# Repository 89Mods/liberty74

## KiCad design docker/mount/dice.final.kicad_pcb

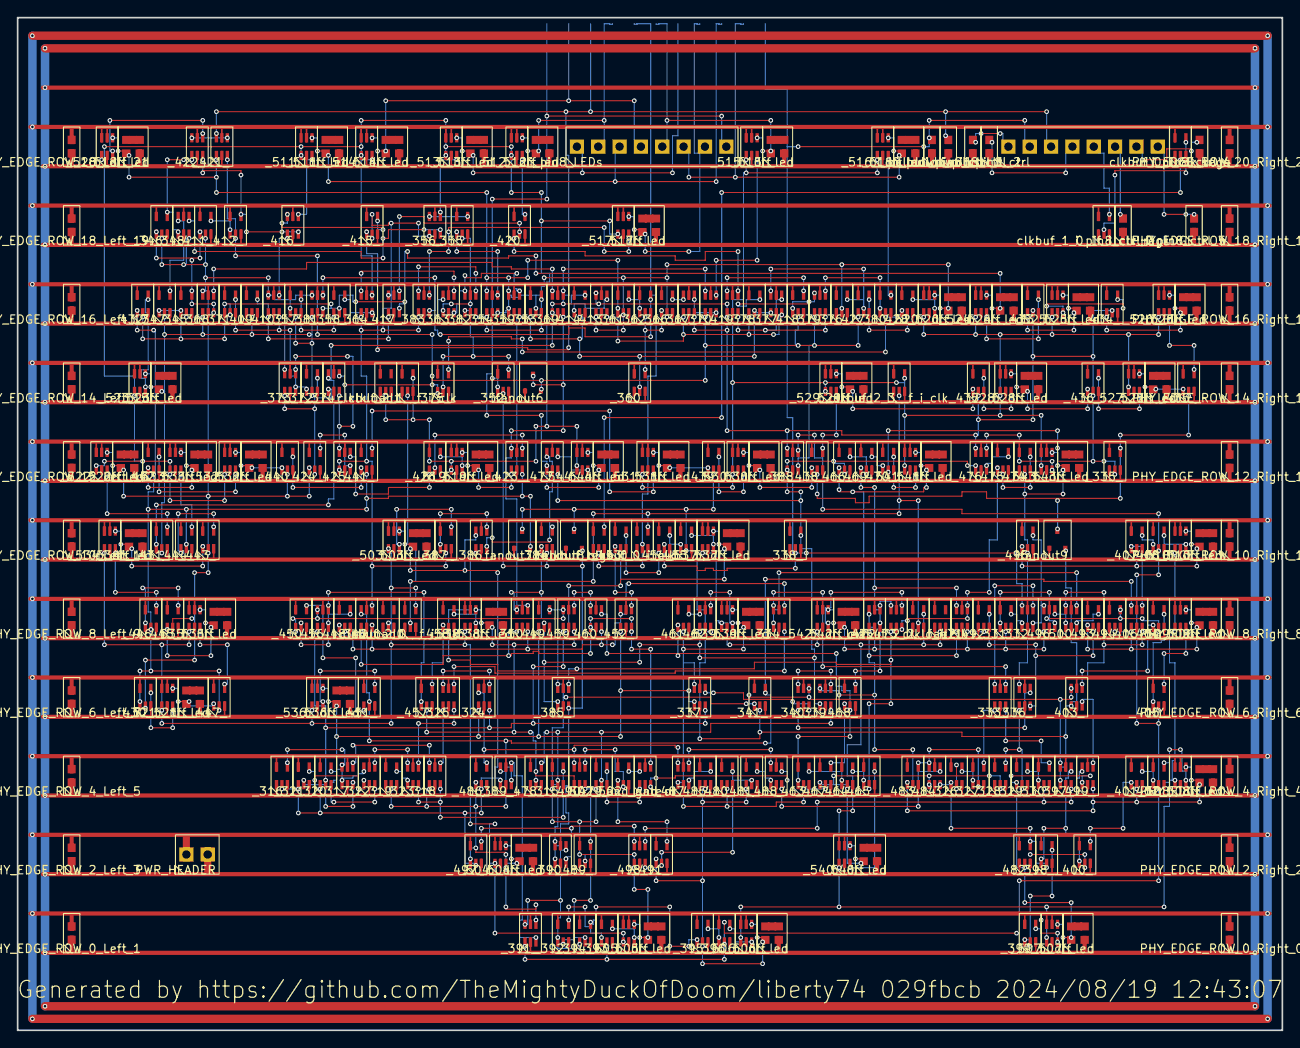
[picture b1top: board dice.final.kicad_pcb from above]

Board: 2 copper layers, 150.5 x 120.5 mm, 313 parts (0 on the bottom side), 246 nets.

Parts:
PHY_EDGE_ROW_0_Left_1, PHY_EDGE_ROW_0_Right_0, PHY_EDGE_ROW_2_Left_3, PHY_EDGE_ROW_2_Right_2, PHY_EDGE_ROW_4_Left_5, PHY_EDGE_ROW_4_Right_4, PHY_EDGE_ROW_6_Left_7, PHY_EDGE_ROW_6_Right_6, PHY_EDGE_ROW_8_Left_9, PHY_EDGE_ROW_8_Right_8, PHY_EDGE_ROW_10_Left_11, PHY_EDGE_ROW_10_Right_10, PHY_EDGE_ROW_12_Left_13, PHY_EDGE_ROW_12_Right_12, PHY_EDGE_ROW_14_Left_15, PHY_EDGE_ROW_14_Right_14, PHY_EDGE_ROW_16_Left_17, PHY_EDGE_ROW_16_Right_16, PHY_EDGE_ROW_18_Left_19, PHY_EDGE_ROW_18_Right_18, PHY_EDGE_ROW_20_Left_21, PHY_EDGE_ROW_20_Right_20: PWR_CAP; PWR_CAP_N
PWR_HEADER: PWR_HEADER; PWR_HEADER_N
_315_, _329_, _357_, _361_, _392_, _395_, _398_, _401_, _404_, _407_, _440_, _443_, _445_, _450_, _453_, _457_, _461_, _464_, _469_, _475_, _483_, _491_, _493_, _495_: XOR2_74LVC1G86; XOR2_74LVC1G86_N
_316_, _319_, _328_, _335_, _338_, _360_, _371_, _376_, _409_, _474_, _478_, _480_, _482_, _485_, _489_, _492_, _494_: INV_74LVC1G04; INV_74LVC1G04_N
_317_, _334_, _336_, _339_, _342_, _359_, _379_, _385_, _391_, _406_, _423_, _425_, _452_, _456_, _459_, _460_, _462_, _473_, _498_, _499_: AND3_74LVC1G11; AND3_74LVC1G11_N
_318_, _323_, _325_, _340_, _350_, _373_, _390_, _397_, _403_, _410_, _417_, _471_: NAND3_74LVC1G10; NAND3_74LVC1G10_N
_320_, _327_, _341_, _362_, _366_, _375_, _393_, _396_, _399_, _402_, _405_, _408_, _414_, _420_, _427_, _430_, _432_, _435_, _438_, _439_, _441_, _442_, _444_, _446_, _447_, _448_, _449_, _451_, _455_, _458_, _463_, _465_, _466_, _467_, _468_, _479_, _481_, _497_, _502__and_gate: AND2_74LVC1G08; AND2_74LVC1G08_N
_321_, _330_, _353_, _355_, _380_, _387_, _394_, _400_, _411_, _412_, _415_, _428_: NOR2_74LVC1G02; NOR2_74LVC1G02_N
_322_, _348_, _354_, _368_, _386_, _500_: MUX2_74LVC1G157; MUX2_74LVC1G157_N
_324_, _381_, _419_: OR3_74LVC1G332; OR3_74LVC1G332_N
_326_, _331_, _347_, _358_, _372_, _378_, _424_, _426_, _431_, _433_, _434_, _436_, _437_, _454_, _470_: OR2_74LVC1G32; OR2_74LVC1G32_N
_332_, _356_, _364_, _370_, _374_, _377_, _383_, _388_, _389_, _416_, _421_, _422_, _472_, _476_, _477_, _484_, _487_, _488_, _490_, _496_, _502__and_or: AO21_74LVC1G0832; AO21_74LVC1G0832_N
_333_, _337_, _363_, _367_, _369_, _382_, _413_: NOR3_74LVC1G27; NOR3_74LVC1G27_N
_345_, _346_, _352_, _384_, _418_, _486_: NAND2_74LVC1G00; NAND2_74LVC1G00_N
_503__dff, _504__dff, _505__dff, _506__dff, _507__dff, _508__dff, _509__dff, _510__dff, _511__dff, _512__dff, _513__dff, _514__dff, _515__dff, _516__dff, _517__dff, _518__dff, _519__dff, _520__dff, _521__dff, _522__dff, _523__dff, _524__dff, _525__dff, _526__dff, _527__dff, _528__dff, _529__dff, _530__dff, _531__dff, _532__dff, _533__dff, _534__dff, _535__dff, _536__dff, _537__dff, _538__dff, _539__dff, _540__dff, _541__dff, _542__dff, _543__dff, _544__dff: DFF_74LVC1G175; DFF_74LVC1G175_N
_503__led, _504__led, _505__led, _506__led, _507__led, _508__led, _509__led, _510__led, _511__led, _512__led, _513__led, _514__led, _515__led, _516__led, _517__led, _518__led, _519__led, _520__led, _521__led, _522__led, _523__led, _524__led, _525__led, _526__led, _527__led, _528__led, _529__led, _530__led, _531__led, _532__led, _533__led, _534__led, _535__led, _536__led, _537__led, _538__led, _539__led, _540__led, _541__led, _542__led, _543__led, _544__led: Led_Res_0603; Led_Res_0603_N
clkbuf_0_i_clk, clkbuf_0_i_clk_regs, clkbuf_1_0__f_i_clk_regs, clkbuf_2_0__f_i_clk, clkbuf_2_1__f_i_clk, clkbuf_2_2__f_i_clk, clkbuf_2_3__f_i_clk: BUF_74LVC1G125; BUF_74LVC1G125_N
clkbuf_regs_0_: BUF_74LVC1G125; BUF_74LVC1G125_N
clkload0, clkload1, clkload2: BUF_74LVC1G125; BUF_74LVC1G125_N
fanout6, fanout7, fanout8, fanout9: DS9809PRSS3; DS9809PRSS3_N
i_pin8_LEDs, i_pin8_ctrl: PINOUT_8; PINOUT_8_N
i_pin8_ctrl_1, i_pin8_ctrl_2, i_pin8_ctrl_3, i_pin8_ctrl_4, i_pin8_ctrl_5: TIE_LO; TIE_LO_N
i_pulldown_roll: PULLDOWN_R0603; PULLDOWN_R0603_N
i_pulldown_rst: PULLDOWN_R0603; PULLDOWN_R0603_N

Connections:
GND: PHY_EDGE_ROW_0_Left_1.1 (GND), PHY_EDGE_ROW_0_Right_0.1 (GND), PHY_EDGE_ROW_2_Left_3.1 (GND), PHY_EDGE_ROW_2_Right_2.1 (GND), PHY_EDGE_ROW_4_Left_5.1 (GND), PHY_EDGE_ROW_4_Right_4.1 (GND), PHY_EDGE_ROW_6_Left_7.1 (GND), PHY_EDGE_ROW_6_Right_6.1 (GND), PHY_EDGE_ROW_8_Left_9.1 (GND), PHY_EDGE_ROW_8_Right_8.1 (GND), PHY_EDGE_ROW_10_Left_11.1 (GND), PHY_EDGE_ROW_10_Right_10.1 (GND), PHY_EDGE_ROW_12_Left_13.1 (GND), PHY_EDGE_ROW_12_Right_12.1 (GND), PHY_EDGE_ROW_14_Left_15.1 (GND), PHY_EDGE_ROW_14_Right_14.1 (GND), PHY_EDGE_ROW_16_Left_17.1 (GND), PHY_EDGE_ROW_16_Right_16.1 (GND), PHY_EDGE_ROW_18_Left_19.1 (GND), PHY_EDGE_ROW_18_Right_18.1 (GND), PHY_EDGE_ROW_20_Left_21.1 (GND), PHY_EDGE_ROW_20_Right_20.1 (GND), PWR_HEADER.2 (GND), _315_.3 (GND), _316_.1 (GND), _316_.3 (GND), _317_.2 (GND), _318_.2 (GND), _319_.1 (GND), _319_.3 (GND), _320_.3 (GND), _321_.3 (GND), _322_.2 (GND), _323_.2 (GND), _324_.2 (GND), _325_.2 (GND), _326_.3 (GND), _327_.3 (GND), _328_.1 (GND), _328_.3 (GND), _329_.3 (GND), _330_.3 (GND), _331_.3 (GND), _332_.2 (GND), _333_.2 (GND), _334_.2 (GND), _335_.1 (GND), _335_.3 (GND), _336_.2 (GND), _337_.2 (GND), _338_.1 (GND), _338_.3 (GND), _339_.2 (GND), _340_.2 (GND), _341_.3 (GND), _342_.2 (GND), _345_.3 (GND), _346_.3 (GND), _347_.3 (GND), _348_.2 (GND), _350_.2 (GND), _352_.3 (GND), _353_.3 (GND), _354_.2 (GND), _355_.3 (GND), _356_.2 (GND), _357_.3 (GND), _358_.3 (GND), _359_.2 (GND), _360_.1 (GND), _360_.3 (GND), _361_.3 (GND), _362_.3 (GND), _363_.2 (GND), _364_.2 (GND), _366_.3 (GND), _367_.2 (GND), _368_.2 (GND), _369_.2 (GND), _370_.2 (GND), _371_.1 (GND), _371_.3 (GND), _372_.3 (GND), _373_.2 (GND), _374_.2 (GND), _375_.3 (GND), _376_.1 (GND), _376_.3 (GND), _377_.2 (GND), _378_.3 (GND), _379_.2 (GND), _380_.3 (GND), _381_.2 (GND), _382_.2 (GND), _383_.2 (GND), _384_.3 (GND), _385_.2 (GND), _386_.2 (GND), _387_.3 (GND), _388_.2 (GND), _389_.2 (GND), _390_.2 (GND), _391_.2 (GND), _392_.3 (GND), _393_.3 (GND), _394_.3 (GND), _395_.3 (GND), _396_.3 (GND), _397_.2 (GND), _398_.3 (GND), _399_.3 (GND), _400_.3 (GND), _401_.3 (GND), _402_.3 (GND), _403_.2 (GND), _404_.3 (GND), _405_.3 (GND), _406_.2 (GND), _407_.3 (GND), _408_.3 (GND), _409_.1 (GND), _409_.3 (GND), _410_.2 (GND), _411_.3 (GND), _412_.3 (GND), _413_.2 (GND), _414_.3 (GND), _415_.3 (GND), _416_.2 (GND), _417_.2 (GND), _418_.3 (GND), _419_.2 (GND), _420_.3 (GND), _421_.2 (GND), _422_.2 (GND), _423_.2 (GND), _424_.3 (GND), _425_.2 (GND), _426_.3 (GND), _427_.3 (GND), _428_.3 (GND), _430_.3 (GND), _431_.3 (GND), _432_.3 (GND), _433_.3 (GND), _434_.3 (GND), _435_.3 (GND), _436_.3 (GND), _437_.3 (GND), _438_.3 (GND), _439_.3 (GND), _440_.3 (GND), _441_.3 (GND), _442_.3 (GND), _443_.3 (GND), _444_.3 (GND), _445_.3 (GND), _446_.3 (GND), _447_.3 (GND), _448_.3 (GND), _449_.3 (GND), _450_.3 (GND), _451_.3 (GND), _452_.2 (GND), _453_.3 (GND), _454_.3 (GND), _455_.3 (GND), _456_.2 (GND), _457_.3 (GND), _458_.3 (GND), _459_.2 (GND), _460_.2 (GND), _461_.3 (GND), _462_.2 (GND), _463_.3 (GND), _464_.3 (GND), _465_.3 (GND), _466_.3 (GND), _467_.3 (GND), _468_.3 (GND), _469_.3 (GND), _470_.3 (GND), _471_.2 (GND), _472_.2 (GND), _473_.2 (GND), _474_.1 (GND), _474_.3 (GND), _475_.3 (GND), _476_.2 (GND), _477_.2 (GND), _478_.1 (GND), _478_.3 (GND), _479_.3 (GND), _480_.1 (GND), _480_.3 (GND), _481_.3 (GND), _482_.1 (GND), _482_.3 (GND), _483_.3 (GND), _484_.2 (GND), _485_.1 (GND), _485_.3 (GND), _486_.3 (GND), _487_.2 (GND), _488_.2 (GND), _489_.1 (GND), _489_.3 (GND), _490_.2 (GND), _491_.3 (GND), _492_.1 (GND), _492_.3 (GND), _493_.3 (GND), _494_.1 (GND), _494_.3 (GND), _495_.3 (GND), _496_.2 (GND), _497_.3 (GND), _498_.2 (GND), _499_.2 (GND), _500_.2 (GND), _502__and_gate.3 (GND), _502__and_or.2 (GND), _503__dff.2 (GND), _503__led.2 (GND), _504__dff.2 (GND), _504__led.2 (GND), _505__dff.2 (GND), _505__led.2 (GND), _506__dff.2 (GND), _506__led.2 (GND), _507__dff.2 (GND), _507__led.2 (GND), _508__dff.2 (GND), _508__led.2 (GND), _509__dff.2 (GND), _509__led.2 (GND), _510__dff.2 (GND), _510__led.2 (GND), _511__dff.2 (GND), _511__led.2 (GND), _512__dff.2 (GND), _512__led.2 (GND), _513__dff.2 (GND), _513__led.2 (GND), _514__dff.2 (GND), _514__led.2 (GND), _515__dff.2 (GND), _515__led.2 (GND), _516__dff.2 (GND), _516__led.2 (GND), _517__dff.2 (GND), _517__led.2 (GND), _518__dff.2 (GND), _518__led.2 (GND), _519__dff.2 (GND), _519__led.2 (GND), _520__dff.2 (GND), _520__led.2 (GND), _521__dff.2 (GND), _521__led.2 (GND), _522__dff.2 (GND), _522__led.2 (GND), _523__dff.2 (GND), _523__led.2 (GND), _524__dff.2 (GND), _524__led.2 (GND), _525__dff.2 (GND), _525__led.2 (GND), _526__dff.2 (GND), _526__led.2 (GND), _527__dff.2 (GND), _527__led.2 (GND), _528__dff.2 (GND), _528__led.2 (GND), _529__dff.2 (GND), _529__led.2 (GND), _530__dff.2 (GND), _530__led.2 (GND), _531__dff.2 (GND), _531__led.2 (GND), _532__dff.2 (GND), _532__led.2 (GND), _533__dff.2 (GND), _533__led.2 (GND), _534__dff.2 (GND), _534__led.2 (GND), _535__dff.2 (GND), _535__led.2 (GND), _536__dff.2 (GND), _536__led.2 (GND), _537__dff.2 (GND), _537__led.2 (GND), _538__dff.2 (GND), _538__led.2 (GND), _539__dff.2 (GND), _539__led.2 (GND), _540__dff.2 (GND), _540__led.2 (GND), _541__dff.2 (GND), _541__led.2 (GND), _542__dff.2 (GND), _542__led.2 (GND), _543__dff.2 (GND), _543__led.2 (GND), _544__dff.2 (GND), _544__led.2 (GND), clkbuf_0_i_clk.1 (GND), clkbuf_0_i_clk.3 (GND), clkbuf_0_i_clk_regs.1 (GND), clkbuf_0_i_clk_regs.3 (GND), clkbuf_1_0__f_i_clk_regs.1 (GND), clkbuf_1_0__f_i_clk_regs.3 (GND), clkbuf_2_0__f_i_clk.1 (GND), clkbuf_2_0__f_i_clk.3 (GND), clkbuf_2_1__f_i_clk.1 (GND), clkbuf_2_1__f_i_clk.3 (GND), clkbuf_2_2__f_i_clk.1 (GND), clkbuf_2_2__f_i_clk.3 (GND), clkbuf_2_3__f_i_clk.1 (GND), clkbuf_2_3__f_i_clk.3 (GND), clkbuf_regs_0_.1 (GND), clkbuf_regs_0_.3 (GND), clkload0.1 (GND), clkload0.3 (GND), clkload1.1 (GND), clkload1.3 (GND), clkload2.1 (GND), clkload2.3 (GND), fanout6.1 (GND), fanout7.1 (GND), fanout8.1 (GND), fanout9.1 (GND), i_pin8_ctrl_1.1 (GND), i_pin8_ctrl_2.1 (GND), i_pin8_ctrl_3.1 (GND), i_pin8_ctrl_4.1 (GND), i_pin8_ctrl_5.1 (GND), i_pulldown_roll.1 (GND), i_pulldown_rst.1 (GND)
ROLL: _332_.6 (C), _338_.2 (A), _454_.2 (A), i_pin8_ctrl.2 (TO_HEADER[1]), i_pulldown_roll.2 (Y)
RST: _335_.2 (A), _367_.3 (B), _369_.1 (A), _374_.6 (C), _388_.6 (C), _413_.6 (C), _419_.1 (A), _421_.6 (C), _431_.1 (B), _433_.2 (A), _434_.2 (A), _436_.2 (A), _437_.2 (A), _470_.2 (A), _476_.6 (C), i_pin8_ctrl.3 (TO_HEADER[2]), i_pulldown_rst.2 (Y)
VDD: PHY_EDGE_ROW_0_Left_1.2 (VDD), PHY_EDGE_ROW_0_Right_0.2 (VDD), PHY_EDGE_ROW_2_Left_3.2 (VDD), PHY_EDGE_ROW_2_Right_2.2 (VDD), PHY_EDGE_ROW_4_Left_5.2 (VDD), PHY_EDGE_ROW_4_Right_4.2 (VDD), PHY_EDGE_ROW_6_Left_7.2 (VDD), PHY_EDGE_ROW_6_Right_6.2 (VDD), PHY_EDGE_ROW_8_Left_9.2 (VDD), PHY_EDGE_ROW_8_Right_8.2 (VDD), PHY_EDGE_ROW_10_Left_11.2 (VDD), PHY_EDGE_ROW_10_Right_10.2 (VDD), PHY_EDGE_ROW_12_Left_13.2 (VDD), PHY_EDGE_ROW_12_Right_12.2 (VDD), PHY_EDGE_ROW_14_Left_15.2 (VDD), PHY_EDGE_ROW_14_Right_14.2 (VDD), PHY_EDGE_ROW_16_Left_17.2 (VDD), PHY_EDGE_ROW_16_Right_16.2 (VDD), PHY_EDGE_ROW_18_Left_19.2 (VDD), PHY_EDGE_ROW_18_Right_18.2 (VDD), PHY_EDGE_ROW_20_Left_21.2 (VDD), PHY_EDGE_ROW_20_Right_20.2 (VDD), PWR_HEADER.1 (VDD), _315_.6 (VDD), _316_.6 (VDD), _317_.5 (VDD), _318_.5 (VDD), _319_.6 (VDD), _320_.6 (VDD), _321_.6 (VDD), _322_.5 (VDD), _323_.5 (VDD), _324_.5 (VDD), _325_.5 (VDD), _326_.6 (VDD), _327_.6 (VDD), _328_.6 (VDD), _329_.6 (VDD), _330_.6 (VDD), _331_.6 (VDD), _332_.5 (VDD), _333_.5 (VDD), _334_.5 (VDD), _335_.6 (VDD), _336_.5 (VDD), _337_.5 (VDD), _338_.6 (VDD), _339_.5 (VDD), _340_.5 (VDD), _341_.6 (VDD), _342_.5 (VDD), _345_.6 (VDD), _346_.6 (VDD), _347_.6 (VDD), _348_.5 (VDD), _350_.5 (VDD), _352_.6 (VDD), _353_.6 (VDD), _354_.5 (VDD), _355_.6 (VDD), _356_.5 (VDD), _357_.6 (VDD), _358_.6 (VDD), _359_.5 (VDD), _360_.6 (VDD), _361_.6 (VDD), _362_.6 (VDD), _363_.5 (VDD), _364_.5 (VDD), _366_.6 (VDD), _367_.5 (VDD), _368_.5 (VDD), _369_.5 (VDD), _370_.5 (VDD), _371_.6 (VDD), _372_.6 (VDD), _373_.5 (VDD), _374_.5 (VDD), _375_.6 (VDD), _376_.6 (VDD), _377_.5 (VDD), _378_.6 (VDD), _379_.5 (VDD), _380_.6 (VDD), _381_.5 (VDD), _382_.5 (VDD), _383_.5 (VDD), _384_.6 (VDD), _385_.5 (VDD), _386_.5 (VDD), _387_.6 (VDD), _388_.5 (VDD), _389_.5 (VDD), _390_.5 (VDD), _391_.5 (VDD), _392_.6 (VDD), _393_.6 (VDD), _394_.6 (VDD), _395_.6 (VDD), _396_.6 (VDD), _397_.5 (VDD), _398_.6 (VDD), _399_.6 (VDD), _400_.6 (VDD), _401_.6 (VDD), _402_.6 (VDD), _403_.5 (VDD), _404_.6 (VDD), _405_.6 (VDD), _406_.5 (VDD), _407_.6 (VDD), _408_.6 (VDD), _409_.6 (VDD), _410_.5 (VDD), _411_.6 (VDD), _412_.6 (VDD), _413_.5 (VDD), _414_.6 (VDD), _415_.6 (VDD), _416_.5 (VDD), _417_.5 (VDD), _418_.6 (VDD), _419_.5 (VDD), _420_.6 (VDD), _421_.5 (VDD), _422_.5 (VDD), _423_.5 (VDD), _424_.6 (VDD), _425_.5 (VDD), _426_.6 (VDD), _427_.6 (VDD), _428_.6 (VDD), _430_.6 (VDD), _431_.6 (VDD), _432_.6 (VDD), _433_.6 (VDD), _434_.6 (VDD), _435_.6 (VDD), _436_.6 (VDD), _437_.6 (VDD), _438_.6 (VDD), _439_.6 (VDD), _440_.6 (VDD), _441_.6 (VDD), _442_.6 (VDD), _443_.6 (VDD), _444_.6 (VDD), _445_.6 (VDD), _446_.6 (VDD), _447_.6 (VDD), _448_.6 (VDD), _449_.6 (VDD), _450_.6 (VDD), _451_.6 (VDD), _452_.5 (VDD), _453_.6 (VDD), _454_.6 (VDD), _455_.6 (VDD), _456_.5 (VDD), _457_.6 (VDD), _458_.6 (VDD), _459_.5 (VDD), _460_.5 (VDD), _461_.6 (VDD), _462_.5 (VDD), _463_.6 (VDD), _464_.6 (VDD), _465_.6 (VDD), _466_.6 (VDD), _467_.6 (VDD), _468_.6 (VDD), _469_.6 (VDD), _470_.6 (VDD), _471_.5 (VDD), _472_.5 (VDD), _473_.5 (VDD), _474_.6 (VDD), _475_.6 (VDD), _476_.5 (VDD), _477_.5 (VDD), _478_.6 (VDD), _479_.6 (VDD), _480_.6 (VDD), _481_.6 (VDD), _482_.6 (VDD), _483_.6 (VDD), _484_.5 (VDD), _485_.6 (VDD), _486_.6 (VDD), _487_.5 (VDD), _488_.5 (VDD), _489_.6 (VDD), _490_.5 (VDD), _491_.6 (VDD), _492_.6 (VDD), _493_.6 (VDD), _494_.6 (VDD), _495_.6 (VDD), _496_.5 (VDD), _497_.6 (VDD), _498_.5 (VDD), _499_.5 (VDD), _500_.5 (VDD), _502__and_gate.6 (VDD), _502__and_or.5 (VDD), _503__dff.5 (VDD), _503__dff.6 (VDD), _504__dff.5 (VDD), _504__dff.6 (VDD), _505__dff.5 (VDD), _505__dff.6 (VDD), _506__dff.5 (VDD), _506__dff.6 (VDD), _507__dff.5 (VDD), _507__dff.6 (VDD), _508__dff.5 (VDD), _508__dff.6 (VDD), _509__dff.5 (VDD), _509__dff.6 (VDD), _510__dff.5 (VDD), _510__dff.6 (VDD), _511__dff.5 (VDD), _511__dff.6 (VDD), _512__dff.5 (VDD), _512__dff.6 (VDD), _513__dff.5 (VDD), _513__dff.6 (VDD), _514__dff.5 (VDD), _514__dff.6 (VDD), _515__dff.5 (VDD), _515__dff.6 (VDD), _516__dff.5 (VDD), _516__dff.6 (VDD), _517__dff.5 (VDD), _517__dff.6 (VDD), _518__dff.5 (VDD), _518__dff.6 (VDD), _519__dff.5 (VDD), _519__dff.6 (VDD), _520__dff.5 (VDD), _520__dff.6 (VDD), _521__dff.5 (VDD), _521__dff.6 (VDD), _522__dff.5 (VDD), _522__dff.6 (VDD), _523__dff.5 (VDD), _523__dff.6 (VDD), _524__dff.5 (VDD), _524__dff.6 (VDD), _525__dff.5 (VDD), _525__dff.6 (VDD), _526__dff.5 (VDD), _526__dff.6 (VDD), _527__dff.5 (VDD), _527__dff.6 (VDD), _528__dff.5 (VDD), _528__dff.6 (VDD), _529__dff.5 (VDD), _529__dff.6 (VDD), _530__dff.5 (VDD), _530__dff.6 (VDD), _531__dff.5 (VDD), _531__dff.6 (VDD), _532__dff.5 (VDD), _532__dff.6 (VDD), _533__dff.5 (VDD), _533__dff.6 (VDD), _534__dff.5 (VDD), _534__dff.6 (VDD), _535__dff.5 (VDD), _535__dff.6 (VDD), _536__dff.5 (VDD), _536__dff.6 (VDD), _537__dff.5 (VDD), _537__dff.6 (VDD), _538__dff.5 (VDD), _538__dff.6 (VDD), _539__dff.5 (VDD), _539__dff.6 (VDD), _540__dff.5 (VDD), _540__dff.6 (VDD), _541__dff.5 (VDD), _541__dff.6 (VDD), _542__dff.5 (VDD), _542__dff.6 (VDD), _543__dff.5 (VDD), _543__dff.6 (VDD), _544__dff.5 (VDD), _544__dff.6 (VDD), clkbuf_0_i_clk.6 (VDD), clkbuf_0_i_clk_regs.6 (VDD), clkbuf_1_0__f_i_clk_regs.6 (VDD), clkbuf_2_0__f_i_clk.6 (VDD), clkbuf_2_1__f_i_clk.6 (VDD), clkbuf_2_2__f_i_clk.6 (VDD), clkbuf_2_3__f_i_clk.6 (VDD), clkbuf_regs_0_.6 (VDD), clkload0.6 (VDD), clkload1.6 (VDD), clkload2.6 (VDD)
_000_: _356_.4 (Y), _513__dff.3 (D)
_001_: _364_.4 (Y), _514__dff.3 (D)
_002_: _370_.4 (Y), _515__dff.3 (D)
_003_: _380_.4 (Y), _516__dff.3 (D)
_004_: _383_.4 (Y), _517__dff.3 (D)
_005_: _387_.4 (Y), _503__dff.3 (D)
_006_: _391_.4 (Y), _504__dff.3 (D)
_007_: _393_.4 (Y), _505__dff.3 (D)
_008_: _396_.4 (Y), _506__dff.3 (D)
_009_: _399_.4 (Y), _507__dff.3 (D)
_010_: _402_.4 (Y), _508__dff.3 (D)
_011_: _405_.4 (Y), _509__dff.3 (D)
_012_: _408_.4 (Y), _510__dff.3 (D)
_013_: _416_.4 (Y), _511__dff.3 (D)
_014_: _420_.4 (Y), _512__dff.3 (D)
_015_: _422_.4 (Y), _518__dff.3 (D)
_016_: _426_.4 (Y), _519__dff.3 (D)
_017_: _428_.4 (Y), _520__dff.3 (D)
_018_: _430_.4 (Y), _521__dff.3 (D)
_019_: _431_.4 (Y), _522__dff.3 (D)
_020_: _432_.4 (Y), _523__dff.3 (D)
_021_: _433_.4 (Y), _524__dff.3 (D)
_022_: _434_.4 (Y), _525__dff.3 (D)
_023_: _435_.4 (Y), _526__dff.3 (D)
_024_: _436_.4 (Y), _527__dff.3 (D)
_025_: _437_.4 (Y), _528__dff.3 (D)
_026_: _438_.4 (Y), _529__dff.3 (D)
_027_: _439_.4 (Y), _530__dff.3 (D)
_028_: _441_.4 (Y), _531__dff.3 (D)
_029_: _442_.4 (Y), _532__dff.3 (D)
_030_: _444_.4 (Y), _533__dff.3 (D)
_031_: _446_.4 (Y), _534__dff.3 (D)
_032_: _447_.4 (Y), _535__dff.3 (D)
_033_: _451_.4 (Y), _536__dff.3 (D)
_034_: _455_.4 (Y), _537__dff.3 (D)
_035_: _458_.4 (Y), _538__dff.3 (D)
_036_: _462_.4 (Y), _539__dff.3 (D)
_037_: _465_.4 (Y), _540__dff.3 (D)
_038_: _470_.4 (Y), _541__dff.3 (D)
_039_: _473_.4 (Y), _542__dff.3 (D)
_040_: _476_.4 (Y), _543__dff.3 (D)
_041_: _477_.4 (Y), _544__dff.3 (D)
_042_: _496_.4 (Y), _500_.1 (I1)
_043_: _390_.3 (B), _497_.4 (Y), _498_.6 (C)
_044_: _330_.2 (A), _397_.3 (B), _498_.4 (Y), _499_.6 (C)
_045_: _403_.3 (B), _406_.3 (B), _499_.4 (Y), _500_.6 (S)
_046_: _334_.1 (A), _500_.4 (Y)
_047_: _315_.4 (Y), _318_.3 (B), _323_.3 (B)
_048_: _316_.4 (Y), _317_.6 (C)
_049_: _317_.4 (Y), _318_.6 (C)
_050_: _318_.4 (Y), _325_.1 (A)
_051_: _319_.4 (Y), _323_.1 (A)
_052_: _320_.4 (Y), _322_.3 (I0)
_053_: _321_.4 (Y), _322_.1 (I1)
_054_: _322_.4 (Y), _323_.6 (C)
_055_: _323_.4 (Y), _325_.3 (B)
_056_: _324_.4 (Y), _325_.6 (C)
_057_: _325_.4 (Y), _334_.3 (B)
_058_: _326_.4 (Y), _327_.1 (B)
_059_: _327_.4 (Y), _333_.1 (A)
_060_: _328_.4 (Y), _329_.2 (A), _336_.1 (A)
_061_: _329_.4 (Y), _330_.1 (B)
_062_: _330_.4 (Y), _333_.3 (B)
_063_: _331_.4 (Y), _332_.1 (A)
_064_: _332_.4 (Y), _333_.6 (C)
_065_: _333_.4 (Y), _334_.6 (C)
_066_: _334_.4 (Y), _342_.3 (B), _350_.3 (B), _448_.1 (B), _452_.6 (C), _460_.3 (B)
_067_: _335_.4 (Y), _435_.2 (A), _438_.2 (A), fanout9.5 (IN)
_068_: _336_.4 (Y), _340_.1 (A)
_069_: _337_.4 (Y), _340_.3 (B)
_070_: _338_.4 (Y), _339_.1 (A), _385_.1 (A), _388_.1 (A), _449_.2 (A), _462_.1 (A), _466_.2 (A), _476_.1 (A), _477_.3 (B)
_071_: _339_.4 (Y), _340_.6 (C)
_072_: _340_.4 (Y), _341_.1 (B), _350_.6 (C), _384_.1 (B), _385_.6 (C), _390_.6 (C), _397_.6 (C), _403_.6 (C)
_073_: _341_.4 (Y), _342_.6 (C), _389_.3 (B), _406_.6 (C), _451_.2 (A)
_074_: _342_.4 (Y), _356_.1 (A), _364_.1 (A), _383_.1 (A), _387_.2 (A), _415_.2 (A), _417_.6 (C), _425_.1 (A)
_077_: _345_.4 (Y), _346_.1 (B), _368_.3 (I0), _411_.1 (B)
_078_: _346_.4 (Y), _348_.1 (I1), _422_.1 (A)
_079_: _347_.4 (Y), _348_.6 (S)
_080_: _348_.4 (Y), _356_.3 (B)
_082_: _350_.4 (Y), _369_.3 (B), _423_.6 (C), fanout6.5 (IN)
_084_: _352_.4 (Y), _355_.2 (A), _363_.1 (A), _375_.2 (A), _382_.1 (A)
_085_: _353_.4 (Y), _354_.1 (I1), _382_.3 (B)
_086_: _354_.4 (Y), _355_.1 (B)
_087_: _355_.4 (Y), _356_.6 (C)
_088_: _357_.4 (Y), _358_.1 (B)
_089_: _358_.4 (Y), _364_.3 (B)
_090_: _359_.4 (Y), _363_.3 (B), _382_.6 (C)
_091_: _360_.4 (Y), _362_.2 (A), _366_.1 (B)
_092_: _361_.4 (Y), _362_.1 (B)
_093_: _362_.4 (Y), _363_.6 (C)
_094_: _363_.4 (Y), _364_.6 (C)
_096_: _366_.4 (Y), _367_.6 (C)
_097_: _367_.4 (Y), _370_.3 (B)
_098_: _368_.4 (Y), _369_.6 (C)
_099_: _369_.4 (Y), _370_.6 (C)
_100_: _371_.4 (Y), _372_.1 (B), _373_.3 (B), _410_.3 (B)
_101_: _372_.4 (Y), _374_.1 (A)
_102_: _373_.4 (Y), _374_.3 (B), _425_.6 (C)
_103_: _374_.4 (Y), _375_.1 (B)
_104_: _375_.4 (Y), _380_.2 (A), _428_.1 (B)
_105_: _376_.4 (Y), _377_.6 (C), _427_.2 (A)
_106_: _377_.4 (Y), _379_.3 (B), _419_.3 (B)
_107_: _378_.4 (Y), _379_.6 (C), _418_.1 (B)
_108_: _379_.4 (Y), _380_.1 (B)
_109_: _381_.4 (Y), _383_.3 (B)
_110_: _382_.4 (Y), _383_.6 (C)
_111_: _384_.4 (Y), _386_.3 (I0), _477_.6 (C)
_112_: _385_.4 (Y), _386_.1 (I1), _458_.2 (A), _465_.2 (A), _473_.1 (A)
_113_: _386_.4 (Y), _387_.1 (B)
_114_: _388_.4 (Y), _391_.1 (A), _393_.2 (A), _396_.2 (A), _399_.2 (A), _402_.2 (A), _405_.2 (A), _408_.2 (A)
_115_: _389_.4 (Y), _391_.3 (B)
_116_: _390_.4 (Y), _391_.6 (C), _392_.1 (B), _394_.1 (B)
_117_: _392_.4 (Y), _393_.1 (B)
_118_: _394_.4 (Y), _395_.1 (B)
_119_: _395_.4 (Y), _396_.1 (B)
_120_: _397_.4 (Y), _398_.1 (B), _400_.1 (B)
_121_: _398_.4 (Y), _399_.1 (B)
_122_: _400_.4 (Y), _401_.1 (B)
_123_: _401_.4 (Y), _402_.1 (B)
_124_: _403_.4 (Y), _404_.1 (B)
_125_: _404_.4 (Y), _405_.1 (B)
_126_: _406_.4 (Y), _407_.1 (B)
_127_: _407_.4 (Y), _408_.1 (B)
_128_: _409_.4 (Y), _410_.1 (A), _417_.1 (A)
_129_: _410_.4 (Y), _416_.1 (A)
_130_: _411_.4 (Y), _412_.1 (B)
_131_: _412_.4 (Y), _416_.3 (B), _422_.3 (B)
_132_: _413_.4 (Y), _414_.1 (B)
_133_: _414_.4 (Y), _415_.1 (B)
_134_: _415_.4 (Y), _416_.6 (C)
_135_: _417_.4 (Y), _420_.2 (A)
_136_: _418_.4 (Y), _419_.6 (C)
_137_: _419_.4 (Y), _420_.1 (B)
_138_: _421_.4 (Y), _422_.6 (C)
_139_: _423_.4 (Y), _426_.2 (A)
_140_: _424_.4 (Y), _425_.3 (B)
_141_: _425_.4 (Y), _426_.1 (B)
_142_: _427_.4 (Y), _428_.2 (A)
_144_: _440_.4 (Y), _441_.1 (B)
_145_: _443_.4 (Y), _444_.1 (B)
_146_: _445_.4 (Y), _446_.1 (B)
_147_: _448_.4 (Y), _450_.2 (A), _456_.3 (B)
_148_: _449_.4 (Y), _450_.1 (B), _456_.6 (C), _459_.6 (C)
_149_: _450_.4 (Y), _451_.1 (B)
_150_: _452_.4 (Y), _453_.1 (B)
_151_: _453_.4 (Y), _454_.1 (B)
_152_: _454_.4 (Y), _455_.1 (B)
_153_: _456_.4 (Y), _457_.1 (B)
_154_: _457_.4 (Y), _458_.1 (B)
_155_: _459_.4 (Y), _460_.6 (C)
_156_: _460_.4 (Y), _461_.1 (B), _463_.1 (B), _468_.2 (A)
_157_: _461_.4 (Y), _462_.6 (C)
_158_: _463_.4 (Y), _464_.1 (B)
_159_: _464_.4 (Y), _465_.1 (B)
_160_: _466_.4 (Y), _469_.2 (A)
_161_: _467_.4 (Y), _468_.1 (B)
_162_: _468_.4 (Y), _469_.1 (B), _471_.6 (C), _472_.3 (B)
_163_: _469_.4 (Y), _470_.1 (B)
_164_: _471_.4 (Y), _473_.3 (B), _475_.1 (B)
_165_: _472_.4 (Y), _473_.6 (C)
_166_: _474_.4 (Y), _475_.2 (A)
_167_: _475_.4 (Y), _476_.3 (B)
_168_: _315_.2 (A), _339_.3 (B), _478_.4 (Y), _479_.2 (A)
_169_: _479_.4 (Y), _502__and_or.1 (A)
_170_: _480_.4 (Y), _481_.2 (A), _491_.2 (A)
_171_: _481_.4 (Y), _488_.1 (A)
_172_: _326_.1 (B), _398_.2 (A), _400_.2 (A), _482_.4 (Y), _484_.3 (B)
_173_: _327_.2 (A), _483_.4 (Y), _484_.6 (C)
_174_: _484_.4 (Y), _488_.3 (B)
_175_: _485_.4 (Y), _487_.3 (B)
_176_: _324_.6 (C), _486_.4 (Y), _487_.6 (C), _490_.6 (C)
_177_: _487_.4 (Y), _488_.6 (C)
_178_: _488_.4 (Y), _502__and_or.3 (B)
_179_: _392_.2 (A), _394_.2 (A), _489_.4 (Y), _490_.3 (B)
_180_: _490_.4 (Y), _502__and_gate.2 (A)
_181_: _491_.4 (Y), _502__and_gate.1 (B)
_183_: _342_.1 (A), _350_.1 (A), _448_.2 (A), _452_.3 (B), _460_.1 (A), _502__and_or.4 (Y)
_184_: _336_.3 (B), _492_.4 (Y), _493_.2 (A)
_185_: _493_.4 (Y), _500_.3 (I0)
_186_: _331_.1 (B), _404_.2 (A), _494_.4 (Y), _496_.3 (B)
_187_: _332_.3 (B), _495_.4 (Y), _496_.6 (C)
_502__a_and: _502__and_gate.4 (Y), _502__and_or.6 (C)
bcd\[0\]: _354_.6 (S), _359_.6 (C), _361_.1 (B), _367_.1 (A), _377_.3 (B), _378_.1 (B), _413_.3 (B), _421_.1 (A), _518__dff.4 (Q), _518__led.1 (I)
bcd\[1\]: _353_.1 (B), _359_.3 (B), _360_.2 (A), _377_.1 (A), _378_.2 (A), _414_.2 (A), _423_.1 (A), _519__dff.4 (Q), _519__led.1 (I)
bcd\[2\]: _353_.2 (A), _354_.3 (I0), _359_.1 (A), _361_.2 (A), _366_.2 (A), _376_.2 (A), _413_.1 (A), _520__dff.4 (Q), _520__led.1 (I)
clkdiv\[0\]: _317_.1 (A), _322_.6 (S), _324_.1 (A), _337_.1 (A), _449_.1 (B), _452_.1 (A), _536__dff.4 (Q), _536__led.1 (I)
clkdiv\[1\]: _317_.3 (B), _320_.2 (A), _321_.2 (A), _324_.3 (B), _337_.3 (B), _453_.2 (A), _456_.1 (A), _459_.1 (A), _537__dff.4 (Q), _537__led.1 (I)
clkdiv\[2\]: _457_.2 (A), _459_.3 (B), _478_.2 (A), _490_.1 (A), _538__dff.4 (Q), _538__led.1 (I)
clkdiv\[3\]: _337_.6 (C), _461_.2 (A), _463_.2 (A), _467_.2 (A), _480_.2 (A), _487_.1 (A), _539__dff.4 (Q), _539__led.1 (I)
clkdiv\[4\]: _326_.2 (A), _328_.2 (A), _464_.2 (A), _467_.1 (B), _484_.1 (A), _540__dff.4 (Q), _540__led.1 (I)
clkdiv\[5\]: _339_.6 (C), _466_.1 (B), _471_.1 (A), _472_.1 (A), _483_.2 (A), _541__dff.4 (Q), _541__led.1 (I)
clkdiv\[6\]: _331_.2 (A), _471_.3 (B), _472_.6 (C), _492_.2 (A), _496_.1 (A), _542__dff.4 (Q), _542__led.1 (I)
clkdiv\[7\]: _336_.6 (C), _474_.2 (A), _495_.2 (A), _543__dff.4 (Q), _543__led.1 (I)
clknet_0_i_clk: clkbuf_0_i_clk.4 (Y), clkbuf_2_0__f_i_clk.2 (A), clkbuf_2_1__f_i_clk.2 (A), clkbuf_2_2__f_i_clk.2 (A), clkbuf_2_3__f_i_clk.2 (A)
clknet_0_i_clk_regs: clkbuf_0_i_clk_regs.4 (Y), clkbuf_1_0__f_i_clk_regs.2 (A)
clknet_1_0__leaf_i_clk_regs: clkbuf_1_0__f_i_clk_regs.4 (Y), i_pin8_ctrl.5 (TO_HEADER[4])
clknet_2_0__leaf_i_clk: _503__dff.1 (CLK), _504__dff.1 (CLK), _505__dff.1 (CLK), _521__dff.1 (CLK), _534__dff.1 (CLK), _535__dff.1 (CLK), _536__dff.1 (CLK), _538__dff.1 (CLK), clkbuf_2_0__f_i_clk.4 (Y), clkload0.2 (A)
clknet_2_1__leaf_i_clk: _511__dff.1 (CLK), _512__dff.1 (CLK), _513__dff.1 (CLK), _514__dff.1 (CLK), _517__dff.1 (CLK), _518__dff.1 (CLK), _519__dff.1 (CLK), _522__dff.1 (CLK), _523__dff.1 (CLK), _532__dff.1 (CLK), _533__dff.1 (CLK), _544__dff.1 (CLK), clkbuf_2_1__f_i_clk.4 (Y), clkload1.2 (A)
clknet_2_2__leaf_i_clk: _506__dff.1 (CLK), _507__dff.1 (CLK), _508__dff.1 (CLK), _509__dff.1 (CLK), _510__dff.1 (CLK), _537__dff.1 (CLK), _539__dff.1 (CLK), _540__dff.1 (CLK), _542__dff.1 (CLK), clkbuf_2_2__f_i_clk.4 (Y), clkload2.2 (A)
clknet_2_3__leaf_i_clk: _515__dff.1 (CLK), _516__dff.1 (CLK), _520__dff.1 (CLK), _524__dff.1 (CLK), _525__dff.1 (CLK), _526__dff.1 (CLK), _527__dff.1 (CLK), _528__dff.1 (CLK), _529__dff.1 (CLK), _530__dff.1 (CLK), _531__dff.1 (CLK), _541__dff.1 (CLK), _543__dff.1 (CLK), clkbuf_2_3__f_i_clk.4 (Y)
counter\[0\]: _316_.2 (A), _320_.1 (B), _321_.1 (B), _386_.6 (S), _389_.1 (A), _486_.2 (A), _497_.2 (A), _503__dff.4 (Q), _503__led.1 (I)
counter\[1\]: _318_.1 (A), _319_.2 (A), _389_.6 (C), _486_.1 (B), _497_.1 (B), _504__dff.4 (Q), _504__led.1 (I)
counter\[2\]: _315_.1 (B), _479_.1 (B), _489_.2 (A), _498_.1 (A), _505__dff.4 (Q), _505__led.1 (I)
counter\[3\]: _395_.2 (A), _481_.1 (B), _485_.2 (A), _491_.1 (B), _498_.3 (B), _506__dff.4 (Q), _506__led.1 (I)
counter\[4\]: _329_.1 (B), _482_.2 (A), _499_.1 (A), _507__dff.4 (Q), _507__led.1 (I)
counter\[5\]: _401_.2 (A), _483_.1 (B), _499_.3 (B), _508__dff.4 (Q), _508__led.1 (I)
counter\[6\]: _406_.1 (A), _493_.1 (B), _494_.2 (A), _509__dff.4 (Q), _509__led.1 (I)
counter\[7\]: _407_.2 (A), _495_.1 (B), _510__dff.4 (Q), _510__led.1 (I)
dp: _477_.1 (A), _544__dff.4 (Q), _544__led.1 (I), i_pin8_LEDs.8 (TO_HEADER[7])
i_clk: clkbuf_0_i_clk.2 (A), clkbuf_regs_0_.2 (A)
i_clk_regs: clkbuf_0_i_clk_regs.2 (A), clkbuf_regs_0_.4 (Y)
lfsr\[0\]: _447_.1 (B), _521__dff.4 (Q), _521__led.1 (I)
lfsr\[1\]: _346_.2 (A), _348_.3 (I0), _357_.1 (B), _368_.6 (S), _373_.6 (C), _381_.6 (C), _410_.6 (C), _411_.2 (A), _424_.1 (B), _430_.2 (A), _440_.2 (A), _443_.2 (A), _445_.2 (A), _522__dff.4 (Q), _522__led.1 (I)
lfsr\[2\]: _345_.2 (A), _347_.2 (A), _357_.2 (A), _368_.1 (I1), _372_.2 (A), _373_.1 (A), _381_.1 (A), _409_.2 (A), _424_.2 (A), _431_.2 (A), _523__dff.4 (Q), _523__led.1 (I)
lfsr\[3\]: _345_.1 (B), _347_.1 (B), _358_.2 (A), _371_.2 (A), _381_.3 (B), _417_.3 (B), _432_.2 (A), _524__dff.4 (Q), _524__led.1 (I)
lfsr\[4\]: _433_.1 (B), _525__dff.4 (Q), _525__led.1 (I)
lfsr\[5\]: _434_.1 (B), _526__dff.4 (Q), _526__led.1 (I)
lfsr\[6\]: _435_.1 (B), _527__dff.4 (Q), _527__led.1 (I)
lfsr\[7\]: _436_.1 (B), _528__dff.4 (Q), _528__led.1 (I)
lfsr\[8\]: _437_.1 (B), _529__dff.4 (Q), _529__led.1 (I)
lfsr\[9\]: _438_.1 (B), _530__dff.4 (Q), _530__led.1 (I)
lfsr\[10\]: _439_.1 (B), _531__dff.4 (Q), _531__led.1 (I)
lfsr\[11\]: _440_.1 (B), _532__dff.4 (Q), _532__led.1 (I)
lfsr\[12\]: _442_.1 (B), _533__dff.4 (Q), _533__led.1 (I)
lfsr\[13\]: _443_.1 (B), _534__dff.4 (Q), _534__led.1 (I)
lfsr\[14\]: _445_.1 (B), _535__dff.4 (Q), _535__led.1 (I)
net1: i_pin8_ctrl.1 (TO_HEADER[0]), i_pin8_ctrl_1.2 (Y)
net2: i_pin8_ctrl.4 (TO_HEADER[3]), i_pin8_ctrl_2.2 (Y)
net3: i_pin8_ctrl.6 (TO_HEADER[5]), i_pin8_ctrl_3.2 (Y)
net4: i_pin8_ctrl.7 (TO_HEADER[6]), i_pin8_ctrl_4.2 (Y)
net5: i_pin8_ctrl.8 (TO_HEADER[7]), i_pin8_ctrl_5.2 (Y)
net6: _352_.1 (B), _370_.1 (A), _379_.1 (A), _388_.3 (B), _412_.2 (A), _418_.2 (A), _421_.3 (B), _427_.1 (B), fanout6.3 (RESET_N)
net7: _423_.3 (B), _430_.1 (B), _432_.1 (B), _441_.2 (A), _442_.2 (A), _444_.2 (A), _446_.2 (A), _447_.2 (A), fanout7.3 (RESET_N)
net8: _352_.2 (A), _384_.2 (A), _385_.3 (B), _390_.1 (A), fanout8.3 (RESET_N)
net9: _341_.2 (A), _397_.1 (A), _403_.1 (A), _439_.2 (A), _455_.2 (A), _462_.3 (B), fanout7.5 (IN), fanout8.5 (IN), fanout9.3 (RESET_N)
segments\[0\]: _513__dff.4 (Q), _513__led.1 (I), i_pin8_LEDs.1 (TO_HEADER[0])
segments\[1\]: _512__dff.4 (Q), _512__led.1 (I), i_pin8_LEDs.2 (TO_HEADER[1])
segments\[2\]: _511__dff.4 (Q), _511__led.1 (I), i_pin8_LEDs.3 (TO_HEADER[2])
segments\[3\]: _514__dff.4 (Q), _514__led.1 (I), i_pin8_LEDs.4 (TO_HEADER[3])
segments\[4\]: _515__dff.4 (Q), _515__led.1 (I), i_pin8_LEDs.5 (TO_HEADER[4])
segments\[5\]: _516__dff.4 (Q), _516__led.1 (I), i_pin8_LEDs.6 (TO_HEADER[5])
segments\[6\]: _517__dff.4 (Q), _517__led.1 (I), i_pin8_LEDs.7 (TO_HEADER[6])
